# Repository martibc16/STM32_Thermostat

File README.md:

# STM32_Thermostat
 A Thermostat with RRS232 comunication

This project involves creating a heating thermostat that interfaces with the user through a 7 segment display to show the current temeprature and the set temperature and two buttons.

The information of the ambient temperature and the set temperature is sent to the controller (see https://github.com/mbc99/heater-controller-v2 for more details on that part) via RS232. 

The microcontroller of this thermostat is a stm32f103c8t6. This is the same microcontroller that is used in the Blue Pill development board which can be found for less than 2€. This gives an economical advantage since the MCU can be found for less than 1€ on Aliexpress.
For simplicity purposes the programing was made using Mbed Studio and using the Mbed OS RTOS to simplify timings and programing.

The PCB was designed using Kicad. The main purpose of using a PCB was to create a circuit as small as possible (since the thermostat was meant to be installed on a living room). A simplified view of the schematic can be seen below (see files for the full kicad project):

As it can be seen the final footprint of the PCB is quite small. Also, the PCB is not completly square to have space for the cable conection (the objective is that the case is small as posible but with a rectangular form)

The circuit is powered by a theoretical 5V supply. However, due to space restraints the PSU is located 9m away from the thermostat and connected to it with thin wires. This means that depending on the power load of the circuit the voltage could fall below accepted values (the 7 seg display needs to be powered with 5V)
To overcome this problem the input supply is fed to a TPS63060 buck-boost converter that outputs stable 5V. Then a linear regulator is used to get 3.3V in order to power the MCU and other iC.

The temperature sensor chosen is the SI7021. Which is a 3.3V I2C temperature and humidty sensor.
For the RS232 comunication the MAX3232 is used.

The 7 segment display is controlled via a TM1637 IC to simplify the displaying of numbers and in order to reduce the component count.

A 3D model of the PCB is showed below:

This model will be later used to create a case for the PCB.

The 3D model of the case was designed using Fusion360.
</p>

</p>

For asthetic purposes the 7 segment display is designed to sit inside the case flushed into its walls. As the model will be printed in white PLA the light will be able to shine through the plastic while the frontal part of the 7segment display will be hidden. This idea is shown on the photo below:
</p>

As you can see the 7 segment display (blue rectangular form) is completly flushed (minus some tolerance) into the case.

The cover is designed to fit into the base with a snap fit.

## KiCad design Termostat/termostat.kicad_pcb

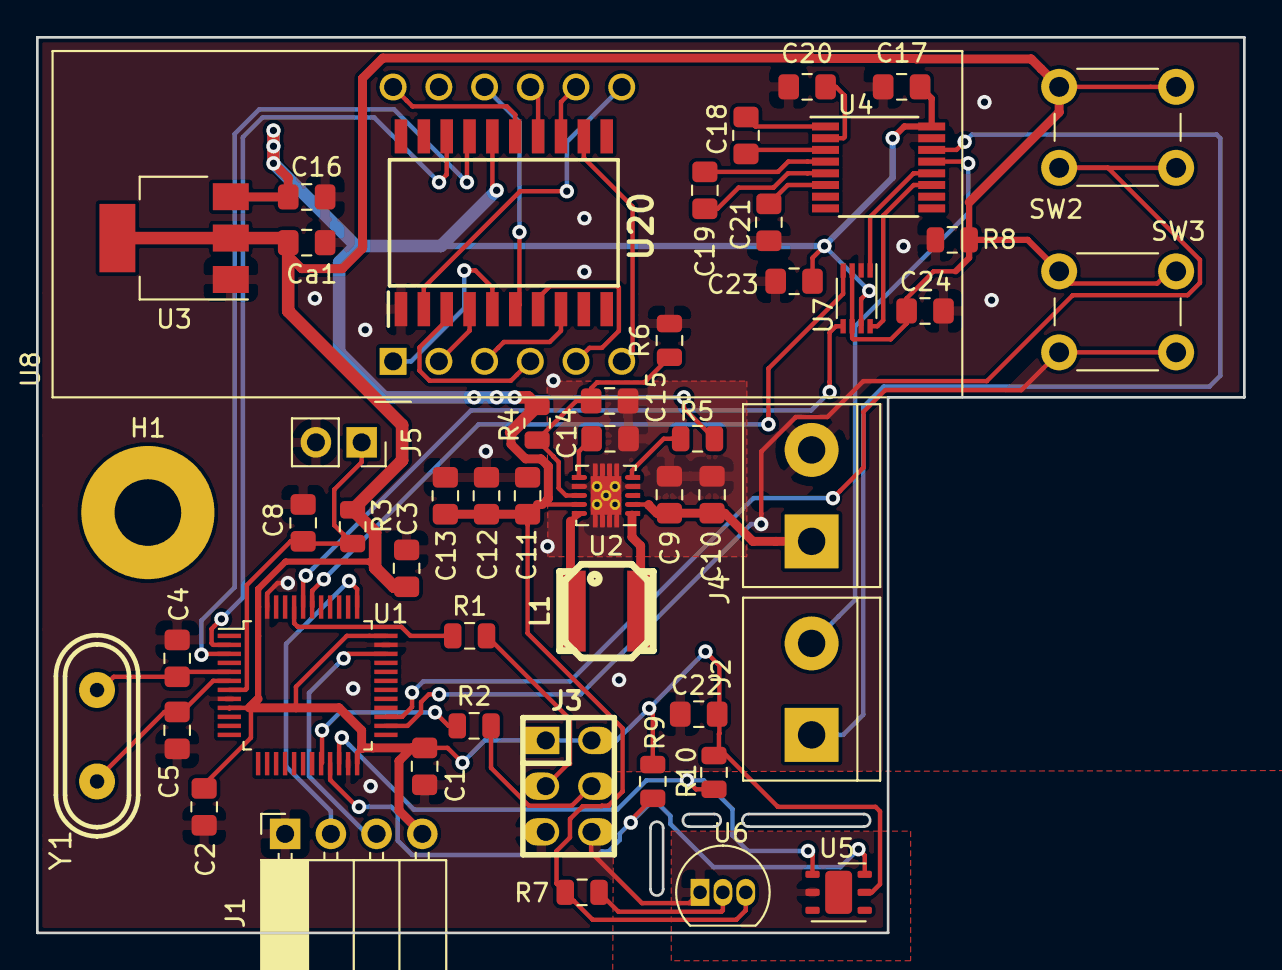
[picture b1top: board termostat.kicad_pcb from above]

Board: 2 copper layers, 67.1 x 49.8 mm, 52 parts (0 on the bottom side), 48 nets.

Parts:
C1, C2, C3, C8, C17, C22, C23, C24: 100n; C_0805_2012Metric_Pad1.15x1.40mm_HandSolder
C4, C5: 12p; C_0805_2012Metric_Pad1.15x1.40mm_HandSolder
C9, C10, C16: 10u; C_0805_2012Metric_Pad1.15x1.40mm_HandSolder
C11, C12, C13: 22u; C_0805_2012Metric_Pad1.15x1.40mm_HandSolder
C14: 0.1u; C_0805_2012Metric_Pad1.15x1.40mm_HandSolder
C15: 10p; C_0805_2012Metric_Pad1.15x1.40mm_HandSolder
C18: 47n; C_0805_2012Metric_Pad1.15x1.40mm_HandSolder
C19, C20, C21: 330n; C_0805_2012Metric_Pad1.15x1.40mm_HandSolder
Ca1: 10u; C_0805_2012Metric_Pad1.15x1.40mm_HandSolder
H1: MountingHole; MountingHole_3.7mm_Pad
J1: Conn_01x04; PinSocket_1x04_P2.54mm_Horizontal
J2, J4: Screw_Terminal_01x02; TerminalBlock_bornier-2_P5.08mm
J3: Conn_02x03_Odd_Even; pin_strip_3x2
J5: Conn_01x02; PinSocket_1x02_P2.54mm_Vertical
L1: 1u; inductor_smd_5x4mm
R1, R2, R3: 100k; R_0805_2012Metric
R4: 1M; R_0805_2012Metric
R5: 10M; R_0805_2012Metric
R6: 111k; R_0805_2012Metric
R7: 4.7K; R_0805_2012Metric
R8, R9, R10: 10k; R_0805_2012Metric
SW2: SW_Push_+but; SW_PUSH_6mm
SW3: SW_Push_-but; SW_PUSH_6mm
U1: STM32F103C8Tx; LQFP-48_7x7mm_P0.5mm
U2: TPS63060; Texas_S-PWSON-N10_ThermalVias
U3: LM1117-3.3; SOT-223-3_TabPin2
U4: MAX3232; TSSOP-16_4.4x5mm_P0.65mm
U5: Si7020-A20; DFN-6-1EP_3x3mm_P1mm_EP1.5x2.4mm
U6: DS18B20; TO-92_Inline
U7: TXS0102DCU; VSSOP-8_2.3x2mm_P0.5mm
U8: CA56-12CGKWA
U20: TM1637_(SOP); SOIC127P1045X280-20N
Y1: 8M; crystal_hc-49s

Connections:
+3V3: C1.1, C2.1, C3.1, C22.1, C24.1, Ca1.1, J1.4, J3.1, J3.2, R3.2, R8.2, R9.2, R10.2, SW2.1, SW3.1, U1.9, U1.24, U1.36, U1.48, U3.2, U5.5, U7.3, U7.6
+5V: C11.1, C12.1, C13.1, C16.1, C17.1, C23.1, R4.1, R5.1, R7.2, U2.9, U3.3, U4.16, U6.3, U7.7, U20.16
/7seg/G1: U8.12, U20.15
/7seg/G2: U8.9, U20.14
/7seg/G3: U8.8, U20.13
/7seg/G4: U8.6, U20.12
/7seg/S2: U8.7, U20.2
/7seg/S3: U8.4, U20.3
/7seg/S4: U8.2, U20.4
/7seg/S5: U8.1, U20.5
/7seg/S6: U8.10, U20.6
/7seg/S7: U8.5, U20.7
/7seg/S8: U8.3, U20.8
/BOOT0: J3.3, R1.2
/BOOT1: J3.4, R2.2
/CLK_7seg: U1.2, U20.18
/Comunication/IN: J2.2, U4.13
/Comunication/OUT: J2.1, U4.14
/Comunication/RX: U4.12, U7.1
/Comunication/TX: U4.11, U7.8
/DCLK: J1.2, U1.37
/DIO: J1.3, U1.34
/DIO_7seg: U1.3, U20.17
/NRST: C8.1, J5.1, R3.1, U1.7
/RX1: U1.42, U7.4
/SCL: R9.1, U1.21, U5.6
/SDA: R10.1, U1.22, U5.1
/Sensing/ONEWIRE: R7.1, U6.2
/TX1: U1.43, U7.5
GND: C1.2, C2.2, C3.2, C4.2, C5.2, C8.2, C9.2, C10.2, C11.2, C12.2, C13.2, C14.2, C15.2, C16.2, C17.2, C20.2, C21.2, C22.2, C23.2, C24.2, Ca1.2, J1.1, J3.5, J3.6, J4.2, J5.2, R6.2, R8.1, U1.8, U1.23, U1.35, U1.47, U2.4, U2.7, U2.11, U3.1, U4.15, U5.2, U6.1, U7.2, U20.1
unnamed: C4.1, U1.5, Y1.1
unnamed: C5.1, U1.6, Y1.2
unnamed: C14.1, U2.6
unnamed: C15.1, R4.2, R6.1, U2.8
unnamed: C18.1, U4.1
unnamed: C18.2, U4.3
unnamed: C19.1, U4.4
unnamed: C19.2, U4.5
unnamed: C20.1, U4.2
unnamed: C21.1, U4.6
unnamed: L1.1, U2.10
unnamed: L1.2, U2.1
unnamed: R1.1, U1.44
unnamed: R2.1, U1.20
unnamed: R5.2, U2.5
unnamed: SW2.2, U1.26
unnamed: SW3.2, U1.27
VCC: C9.1, C10.1, J4.1, U2.2

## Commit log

2020-03-10 photos
